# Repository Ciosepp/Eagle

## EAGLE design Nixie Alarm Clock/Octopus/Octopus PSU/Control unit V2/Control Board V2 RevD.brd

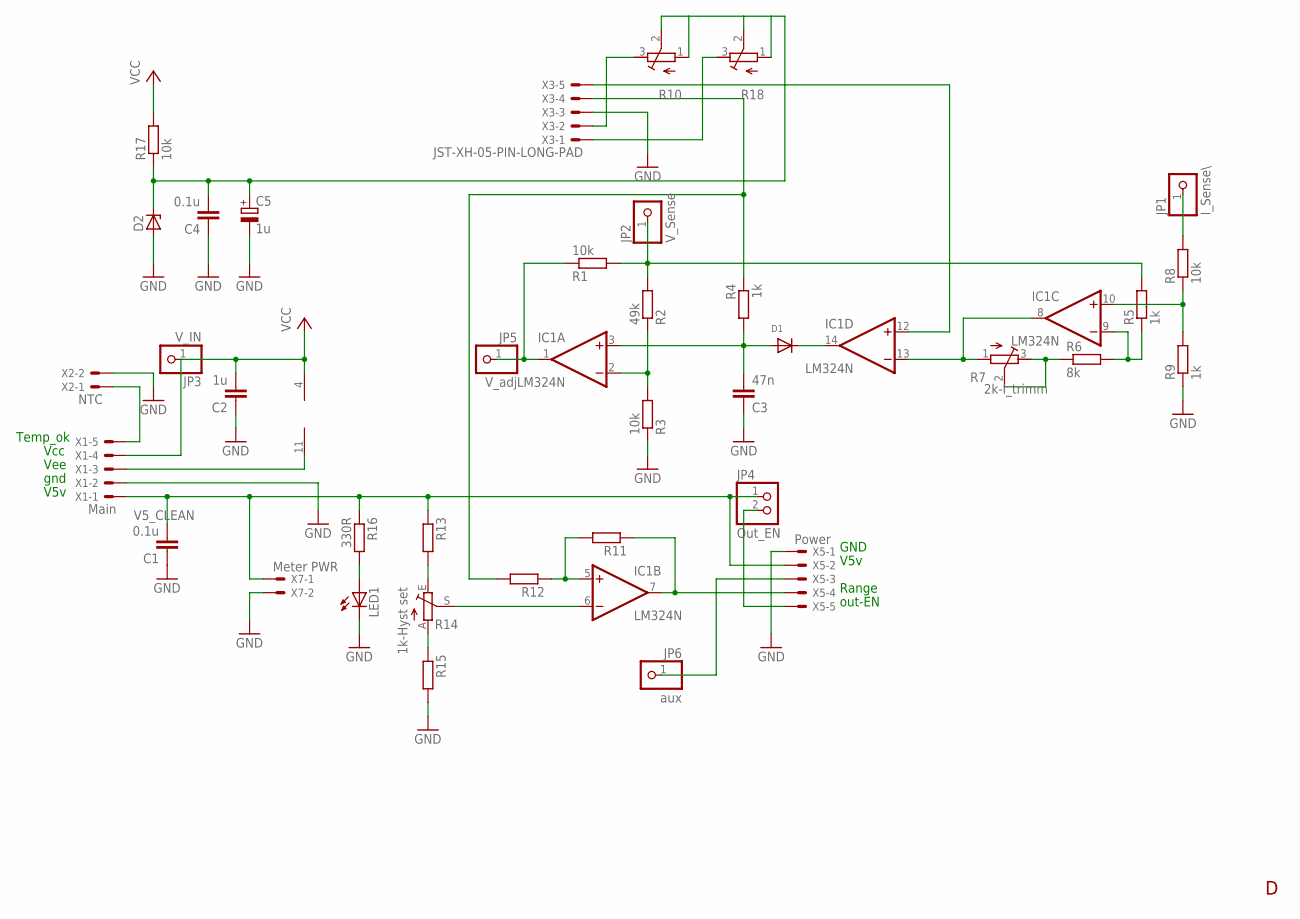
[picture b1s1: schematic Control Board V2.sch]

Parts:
C1, C4: 0.1u; C050-025X075
C2: 1u; C050-025X075
C3: 47n; C050-025X075
C5: 1u; E5-10,5
D1: DIODEDO-1N4148; DO-1N4148
D2: ZENER-DIODEDO35Z10; DO35Z10
IC1: LM324N; DIL14
JP1: I_Sense\; 1X01
JP2: V_Sense; 1X01
JP3: V_IN; 1X01
JP4: Out_EN; 1X02
JP5: V_adj; 1X01
JP6: aux; 1X01
LED1: LED3MM
R1, R3, R8, R17: 10k; 0204/7
R2: 49k; 0204/7
R4, R9: 1k; 0204/7
R5: 1k; 0204/5
R6: 8k; 0204V
R7: 2k-I_trimm; RTRIM64W
R10, R18: R-TRIMM64W; RTRIM64W
R11: R-EU_0204/5; 0204/5
R12, R13: R-EU_0204/2V; 0204V
R14: 1k-Hyst set; B25P
R15: R-EU_0204/7; 0204/7
R16: 330R; 0207/2V
X1: Main; JST-XH-05-PACKAGE-LONG-PAD
X2: NTC; JST-XH-02-PACKAGE-LONG-PAD
X3: JST-XH-05-PIN-LONG-PAD; JST-XH-05-PACKAGE-LONG-PAD
X5: Power; JST-XH-05-PACKAGE-LONG-PAD
X7: Meter PWR; JST-XH-02-PACKAGE-LONG-PAD

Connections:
GND: C1.1, C2.1, C3.1, C4.1, C5.-, D2.A, LED1.K (C), R3.1, R9.1, R15.2, X1.2, X2.2, X3.3, X5.1, X7.2
unnamed: D1.C, IC1.14 (OUT)
unnamed: X1.5, X2.1
unnamed: IC1.1 (OUT), JP5.1, R1.1
unnamed: JP6.1, X5.3
unnamed: IC1.2 (-IN), R2.1, R3.2
unnamed: C3.2, D1.A, IC1.3 (+IN), R4.2
unnamed: JP4.2, X5.5
unnamed: R6.1, R7.2 (S), R7.3 (E)
unnamed: IC1.9 (-IN), R5.1, R6.2
unnamed: IC1.8 (OUT), IC1.13 (-IN), R7.1 (A)
unnamed: JP1.1, R8.2
unnamed: LED1.A, R16.2
unnamed: IC1.11 (V-), X1.3
unnamed: IC1.12 (+IN), X3.5
unnamed: IC1.6 (-IN), R14.S
unnamed: R10.3 (E), X3.2
unnamed: R18.3 (E), X3.1
unnamed: JP2.1, R1.2, R2.2, R5.2
unnamed: IC1.7 (OUT), R11.1, X5.4
unnamed: IC1.5 (+IN), R11.2, R12.1
unnamed: R13.2, R14.E
unnamed: C4.2, C5.+, D2.C, R10.1 (A), R10.2 (S), R17.1, R18.1 (A), R18.2 (S)
unnamed: R14.A, R15.1
unnamed: R4.1, R12.2, X3.4
unnamed: IC1.10 (+IN), R8.1, R9.2
V5_CLEAN: C1.2, JP4.1, R13.1, R16.1, X1.1, X5.2, X7.1
VCC: C2.2, IC1.4 (V+), JP3.1, R17.2, X1.4

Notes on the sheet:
out-EN
GND
Range
Vcc
Vee
gnd
V5v
Temp_ok

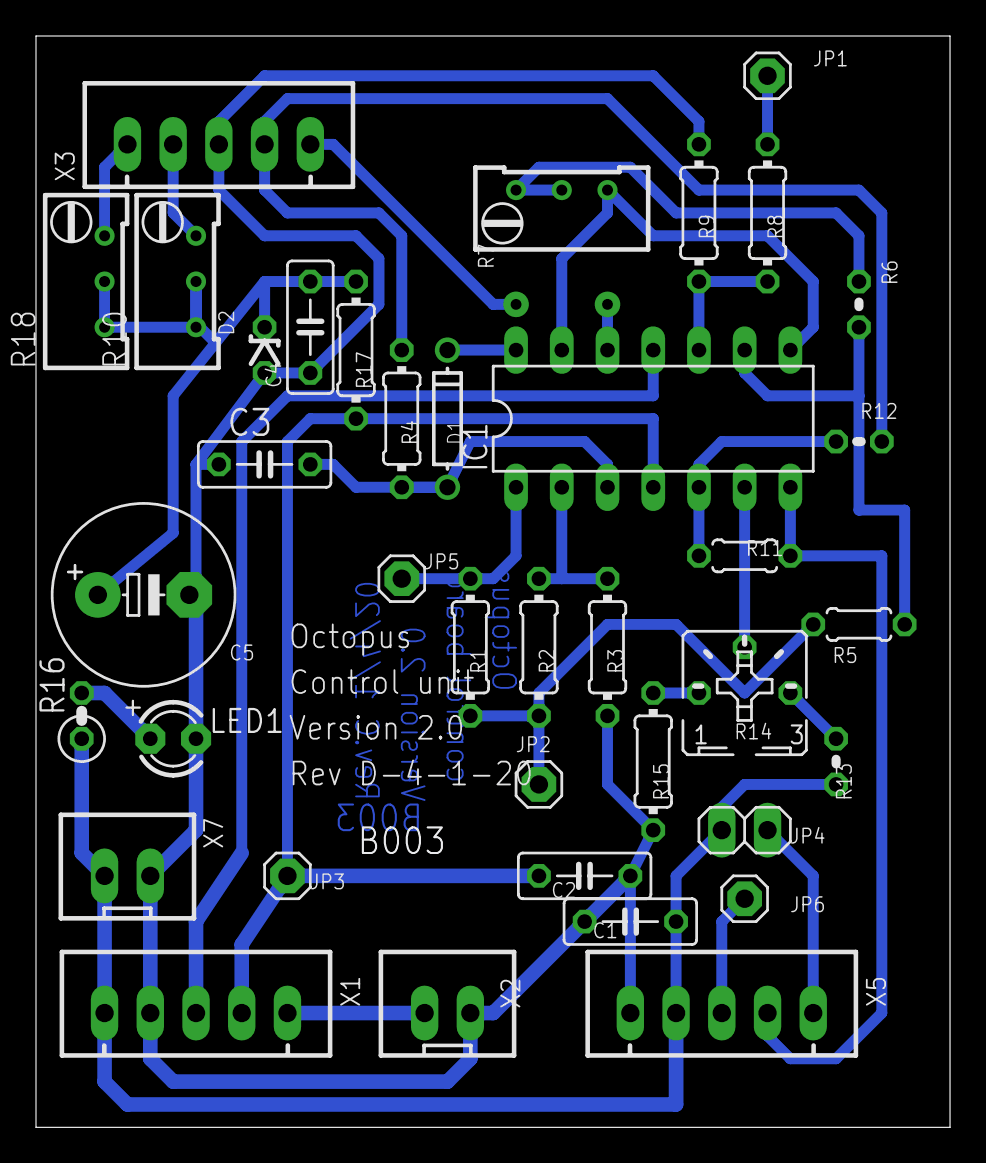
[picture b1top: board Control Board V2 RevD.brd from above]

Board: 2 copper layers, 50.8 x 60.6 mm, 38 parts (0 on the bottom side), 28 nets.

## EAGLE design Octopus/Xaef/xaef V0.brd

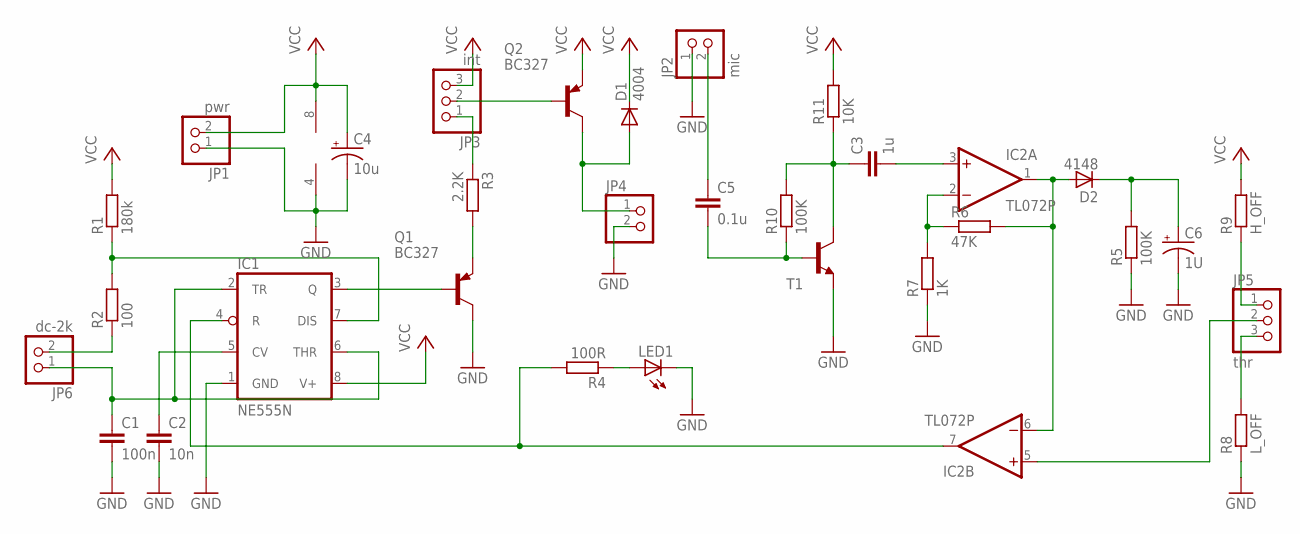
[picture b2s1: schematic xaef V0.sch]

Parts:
C1: 100n; C050-030X075
C2: 10n; C050-030X075
C3: 1u; C050-030X075
C4: 10u; E3,5-8
C5: 0.1u; C050-025X075
C6: 1U; E3,5-8
D1: 4004; D-2.5
D2: 4148; DIODE_DO35-7
IC1: NE555N; DIL08-ROUND
IC2: TL072P; DIL08
JP1: pwr; 1X02
JP2: mic; 1X02
JP3: int; 1X03
JP4: PINHD-1X2; 1X02
JP5: thr; 1X03
JP6: dc-2k; 1X02
LED1: LED5MM
Q1, Q2: BC327; TO92-EBC
R1: 180k; 0207/2V
R2: 100; 0207/2V
R3: 2.2K; 0207/2V
R4: 100R; 0207/2V
R5, R10: 100K; 0207/2V
R6: 47K; 0207/2V
R7: 1K; 0207/2V
R8: L_OFF; 0207/2V
R9: H_OFF; 0207/2V
R11: 10K; 0207/2V
T1: 2N3904-NPN-TO92-EBC; TO92-EBC

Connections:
GND: C1.2, C2.2, C4.-, C6.-, IC1.1 (GND), IC2.4 (V-), JP1.1, JP2.1, JP4.2, LED1.K (C), Q1.C, R5.1, R7.1, R8.1, T1.E
unnamed: IC1.7 (DIS), R1.1, R2.2
unnamed: IC1.3 (Q), Q1.B
unnamed: JP3.2, Q2.B
unnamed: Q1.E, R3.2
unnamed: D1.A, JP4.1, Q2.C
unnamed: C2.1, IC1.5 (CV)
unnamed: C1.1, IC1.2 (TR), IC1.6 (THR), JP6.1
unnamed: LED1.A, R4.1
unnamed: IC1.4 (R), IC2.7 (OUT), R4.2
unnamed: JP3.1, R3.1
unnamed: IC2.2 (-IN), R6.1, R7.2
unnamed: JP6.2, R2.1
unnamed: D2.A (C), IC2.1 (OUT), IC2.6 (-IN), R6.2
unnamed: C3.2, IC2.3 (+IN)
unnamed: C3.1, R10.2, R11.1, T1.C
unnamed: JP5.3, R8.2
unnamed: JP5.1, R9.1
unnamed: C5.2, R10.1, T1.B
unnamed: IC2.5 (+IN), JP5.2
unnamed: C6.+, D2.C (A), R5.2
unnamed: C5.1, JP2.2
VCC: C4.+, D1.C, IC1.8 (V+), IC2.8 (V+), JP1.2, JP3.3, Q2.E, R1.2, R9.2, R11.2

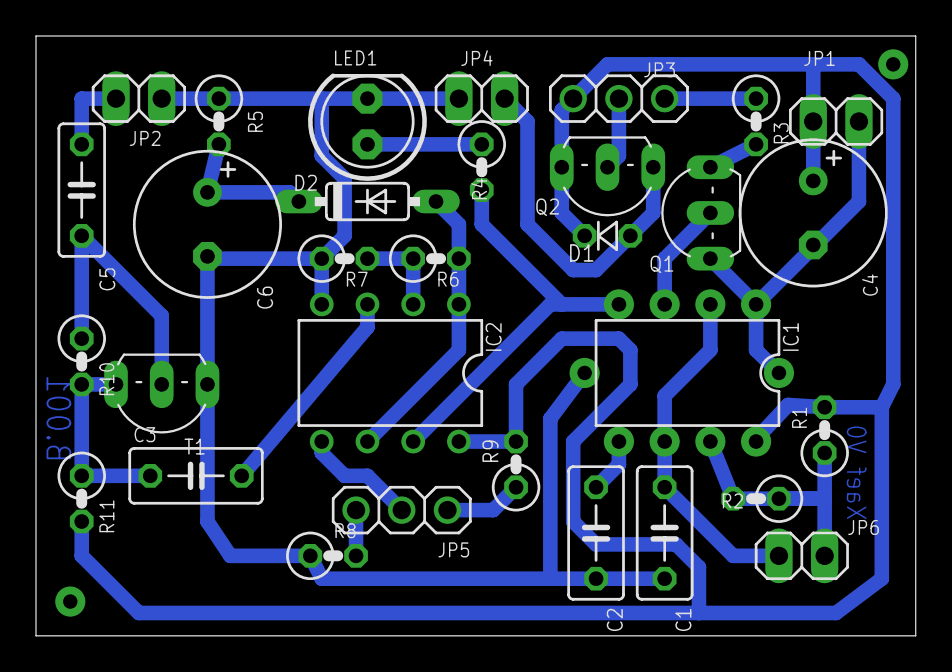
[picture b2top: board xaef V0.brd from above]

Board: 2 copper layers, 48.9 x 33.3 mm, 31 parts (0 on the bottom side), 23 nets.

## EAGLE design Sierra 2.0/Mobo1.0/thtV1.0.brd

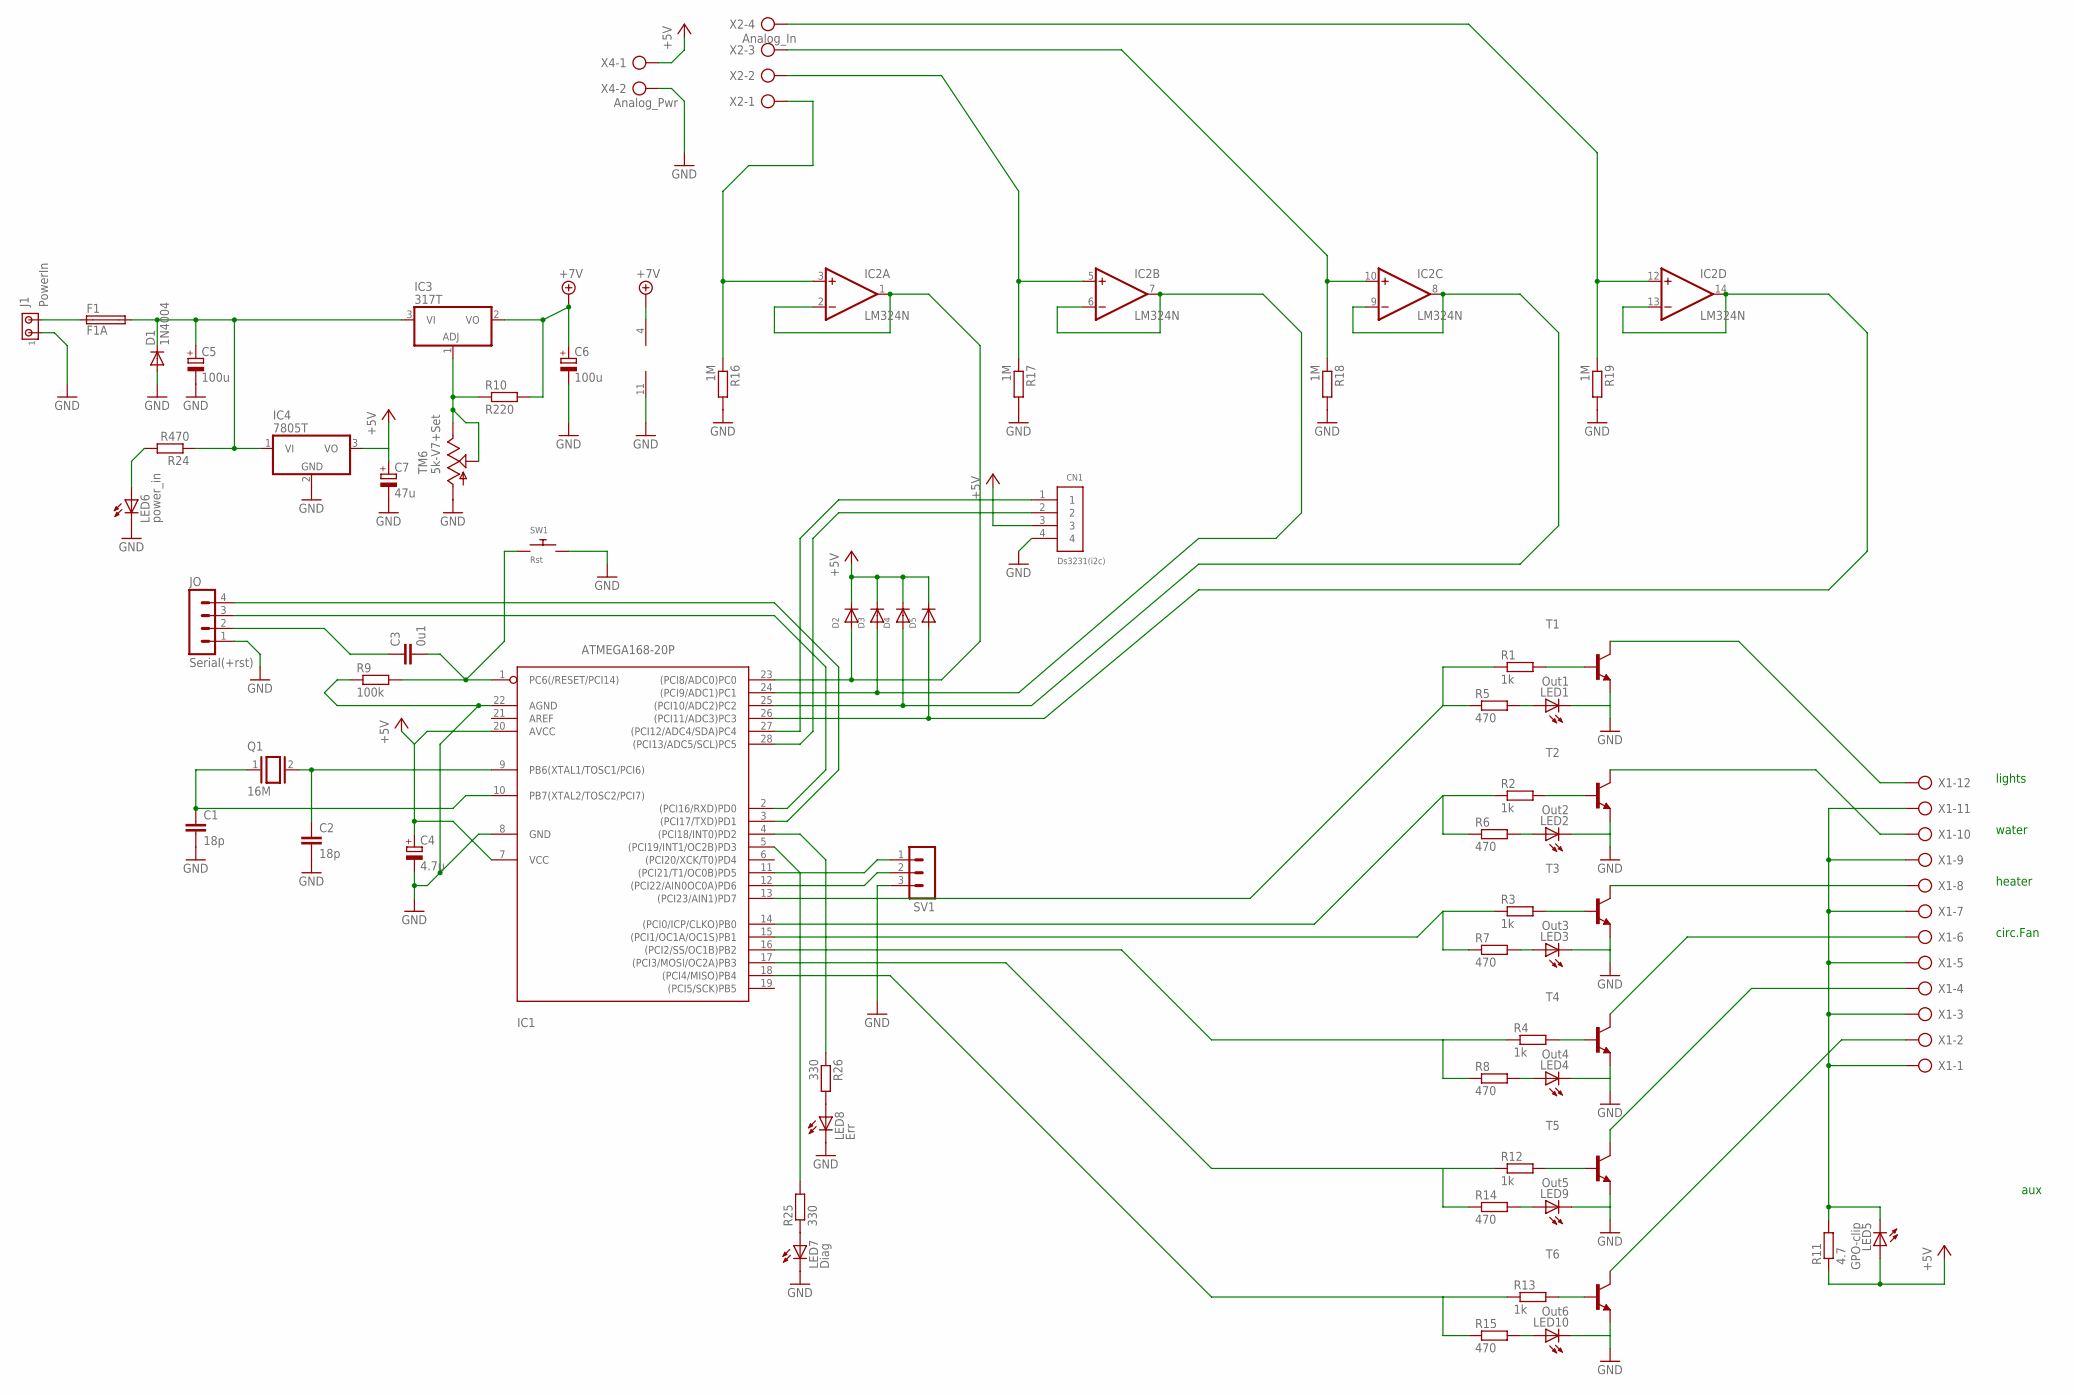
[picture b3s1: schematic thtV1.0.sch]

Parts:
C1, C2: 18p; C025-024X044
C3: 0u1; C050-030X075
C4: 4.7u; E5-10,5
C5: 100u; E5-10,5
C6: 100u; E3,5-8
C7: 47u; E2,5-6E
CN1: Ds3231(i2c); 1X04-BIG
D1: 1N4004; DO41-10
D2, D3, D4, D5: DIODEDO-1N4148; DO-1N4148
F1: F1A; GSH15
IC1: ATMEGA168-20P; DIL28-3
IC2: LM324N; DIL14
IC3: 317T; TO220H
IC4: 7805T; TO220H
J1: PowerIn; 1X2MTA
JO: Serial(+rst); MA04-1
LED1: Out1; LED3MM
LED2: Out2; LED3MM
LED3: Out3; LED3MM
LED4: Out4; LED3MM
LED5: GPO-clip; LED3MM
LED6: power_in; LED3MM
LED7: Diag; LED3MM
LED8: Err; LED3MM
LED9: Out5; LED3MM
LED10: Out6; LED3MM
Q1: 16M; QS
R1, R2, R3, R4, R12, R13: 1k; 0207/10
R5, R6, R7, R8, R14, R15: 470; 0204V
R9: 100k; 0207/10
R10: R220; 0207/10
R11: 4.7; 0207/10
R16, R17, R18, R19: 1M; 0204V
R24: R470; 0207/10
R25, R26: 330; 0207/2V
SV1: MA03-1
SW1: Rst; TACT_PANA-EVQ
T1, T2, T3, T4, T5, T6: BC547A-NPN-TO92-CBE; TO92-CBE
TM6: 5k-V7+Set; 6MM
X1: AK300/12
X2: Analog_In; AK300/4
X4: Analog_Pwr; AK300/2

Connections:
+5V: C4.+, C7.+, CN1.3, D2.C, D3.C, D4.C, D5.C, IC1.7 (VCC), IC1.20 (AVCC), IC4.3 (VO), LED5.A, R11.1, X4.1
+7V: C6.+, IC2.4 (V+), IC3.2 (VO), R10.2
GND: C1.2, C2.2, C4.-, C5.-, C6.-, C7.-, CN1.4, D1.A, IC1.8 (GND), IC1.22 (AGND), IC2.11 (V-), IC4.2 (GND), J1.1, JO.1, LED1.K (C), LED2.K (C), LED3.K (C), LED4.K (C), LED6.K (C), LED7.K (C), LED8.K (C), LED9.K (C), LED10.K (C), R9.1, R16.2, R17.2, R18.2, R19.2, SV1.3, SW1.P$2, T1.E, T2.E, T3.E, T4.E, T5.E, T6.E, TM6.A, X4.2
unnamed: C2.1, IC1.9 (PB6(XTAL1/TOSC1/PCI6)), Q1.2
unnamed: C1.1, IC1.10 (PB7(XTAL2/TOSC2/PCI7)), Q1.1
unnamed: R4.2, T4.B
unnamed: R3.2, T3.B
unnamed: LED8.A, R26.2
unnamed: LED3.A, R7.2
unnamed: LED2.A, R6.2
unnamed: LED1.A, R5.2
unnamed: LED4.A, R8.2
unnamed: R1.2, T1.B
unnamed: R2.2, T2.B
unnamed: IC1.16 ((PCI2/SS/OC1B)PB2), R4.1, R8.1
unnamed: IC2.10 (+IN), R18.1, X2.3
unnamed: IC1.15 ((PCI1/OC1A/OC1S)PB1), R3.1, R7.1
unnamed: IC1.14 ((PCI0/ICP/CLKO)PB0), R2.1, R6.1
unnamed: D3.A, IC1.24 ((PCI9/ADC1)PC1), IC2.6 (-IN), IC2.7 (OUT)
unnamed: IC1.5 ((PCI19/INT1/OC2B)PD3), R25.2
unnamed: IC1.4 ((PCI18/INT0)PD2), R26.1
unnamed: C3.1, JO.2
unnamed: IC3.1 (ADJ), R10.1, TM6.E, TM6.S
unnamed: IC1.2 ((PCI16/RXD)PD0), JO.3
unnamed: IC1.3 ((PCI17/TXD)PD1), JO.4
unnamed: F1.1, J1.2
unnamed: C5.+, D1.C, F1.2, IC3.3 (VI), IC4.1 (VI), R24.1
unnamed: C3.2, IC1.1 (PC6(/RESET/PCI14)), R9.2, SW1.P$1
unnamed: R13.2, T6.B
unnamed: R12.2, T5.B
unnamed: T1.C, X1.12
unnamed: T2.C, X1.10
unnamed: T3.C, X1.8
unnamed: T4.C, X1.6
unnamed: LED5.K (C), R11.2, X1.1, X1.3, X1.5, X1.7, X1.9, X1.11
unnamed: LED9.A, R14.2
unnamed: IC2.5 (+IN), R17.1, X2.2
unnamed: IC2.12 (+IN), R19.1, X2.4
unnamed: D2.A, IC1.23 ((PCI8/ADC0)PC0), IC2.1 (OUT), IC2.2 (-IN)
unnamed: LED10.A, R15.2
unnamed: D4.A, IC1.25 ((PCI10/ADC2)PC2), IC2.8 (OUT), IC2.9 (-IN)
unnamed: D5.A, IC1.26 ((PCI11/ADC3)PC3), IC2.13 (-IN), IC2.14 (OUT)
unnamed: IC1.18 ((PCI4/MISO)PB4), R13.1, R15.1
unnamed: IC1.17 ((PCI3/MOSI/OC2A)PB3), R12.1, R14.1
unnamed: IC2.3 (+IN), R16.1, X2.1
unnamed: T5.C, X1.4
unnamed: T6.C, X1.2
unnamed: LED6.A, R24.2
unnamed: LED7.A, R25.1
unnamed: CN1.1, IC1.27 ((PCI12/ADC4/SDA)PC4)
unnamed: CN1.2, IC1.28 ((PCI13/ADC5/SCL)PC5)
unnamed: IC1.11 ((PCI21/T1/OC0B)PD5), SV1.1
unnamed: IC1.13 ((PCI23/AIN1)PD7), R1.1, R5.1
unnamed: IC1.12 ((PCI22/AIN0OC0A)PD6), SV1.2

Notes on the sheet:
lights
water
heater
circ.Fan
aux

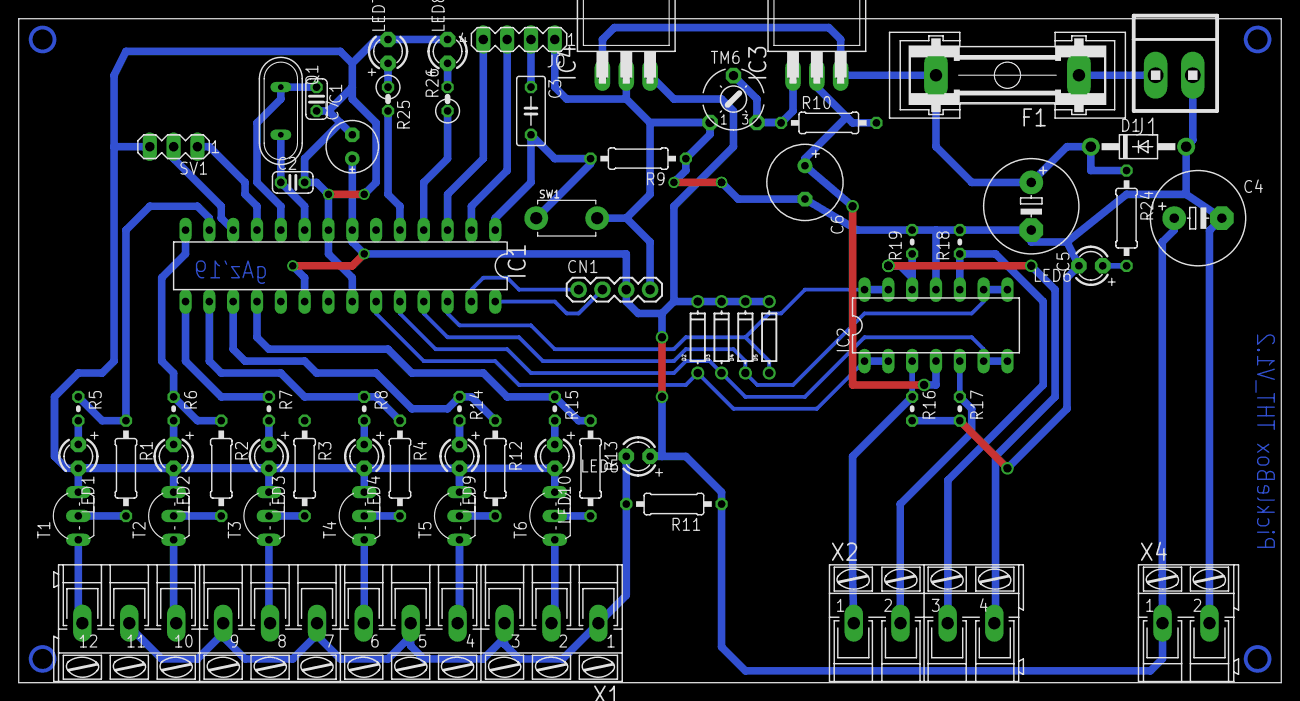
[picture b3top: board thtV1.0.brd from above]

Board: 2 copper layers, 134.6 x 70.8 mm, 65 parts (0 on the bottom side), 54 nets.

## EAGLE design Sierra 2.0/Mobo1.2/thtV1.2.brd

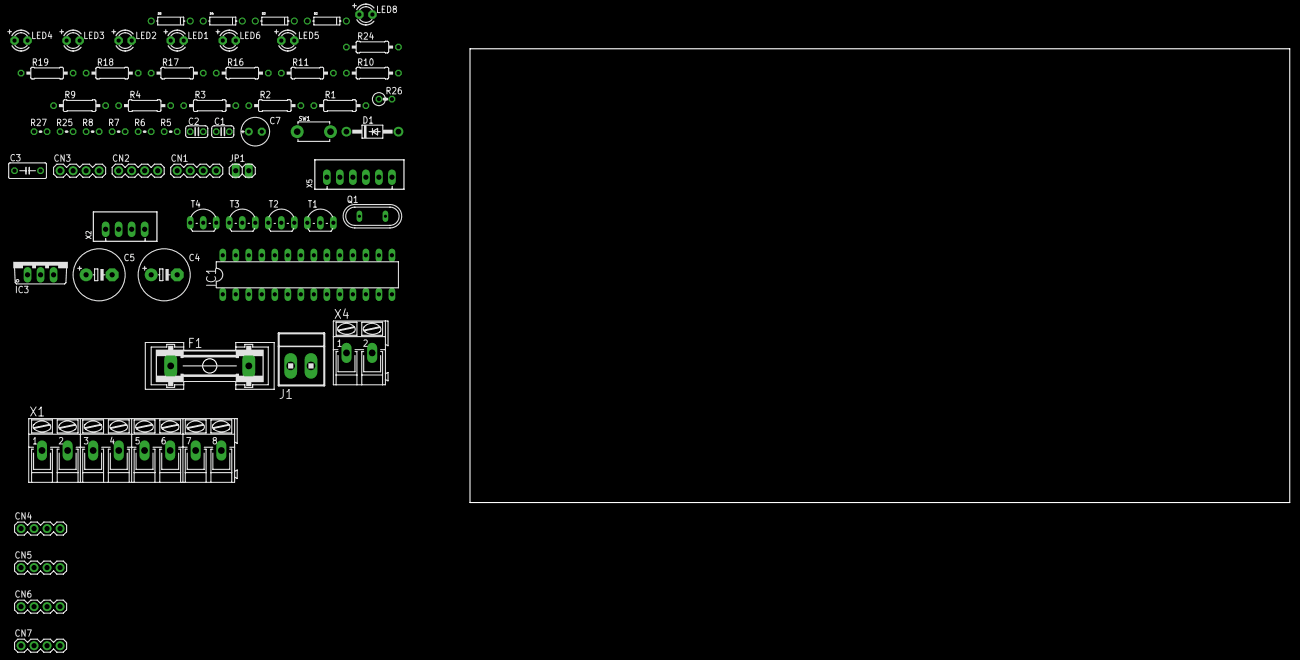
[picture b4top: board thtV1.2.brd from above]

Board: 2 copper layers, 160.0 x 88.6 mm, 59 parts (0 on the bottom side), 42 nets, no tracks yet.

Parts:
C1, C2: 18p; C025-024X044
C3: 0u1; C050-030X075
C4: 4.7u; E5-10,5
C5: 100u; E5-10,5
C7: 47u; E2,5-6E
CN1: Ds3231(i2c); 1X04-BIG
CN2: I2C-GPO; 1X04-BIG
CN3: I2C-APU; 1X04-BIG
CN4, CN5, CN6, CN7: 1X4-BIG; 1X04-BIG
D1: 1N4004; DO41-10
D2, D3, D4, D5: DO-1N4148
F1: F1A; GSH15
IC1: ATMEGA328; DIL28-3
IC3: 7805TV; TO220V
J1: PowerIn; 1X2MTA
JP1: Main Pushbutton; 1X02
LED1: Out1; LED3MM
LED2: Out2; LED3MM
LED3: Out3; LED3MM
LED4: Out4; LED3MM
LED5: GPO-clip; LED3MM
LED6: pwr_ok; LED3MM
LED8: Err; LED3MM
Q1: 16M; QS
R1, R2, R3, R4: 1k; 0207/10
R5, R6, R7, R8: 470; 0204V
R9: 100k; 0207/10
R10: 0R1; 0207/10
R11: 4R7; 0207/10
R16, R17, R18, R19: 1M; 0207/10
R24: 470; 0207/10
R25, R27: 10k; 0204V
R26: 330; 0207/2V
SW1: Rst; TACT_PANA-EVQ
T1, T2, T3, T4: 2N2222; TO92-EBC-OVAL
X1: GPO; AK300/8
X2: Serial_port; JST-XH-04-PACKAGE-LONG-PAD
X4: Analog_Pwr; AK300/2
X5: Sd_module; JST-XH-06-PACKAGE-LONG-PAD

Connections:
+5V: C4.+, C7.+, CN1.3, CN2.3, CN3.3, CN4.3, CN5.3, CN6.3, CN7.3, D2.C, D3.C, D4.C, D5.C, IC1.7, IC1.20, IC3.3, LED5.A, R10.2, R11.1, R25.1, R27.1, X5.2
GND: C1.2, C2.2, C4.-, C5.-, C7.-, CN1.4, CN2.4, CN3.4, CN4.4, CN5.4, CN6.4, CN7.4, D1.A, IC1.8, IC1.22, IC3.2, J1.1, JP1.2, LED1.K, LED2.K, LED3.K, LED4.K, LED6.K, LED8.K, R9.1, R16.2, R17.2, R18.2, R19.2, SW1.P$2, T1.E, T2.E, T3.E, T4.E, X2.1, X4.2, X5.1
I2C_SCL: CN1.2, CN2.2, CN3.2, IC1.28, R27.2
I2C_SDA: CN1.1, CN2.1, CN3.1, IC1.27, R25.2
unnamed: C2.1, IC1.9, Q1.2
unnamed: R4.2, T4.B
unnamed: R3.2, T3.B
unnamed: LED8.A, R26.2
unnamed: LED3.A, R7.2
unnamed: LED2.A, R6.2
unnamed: LED1.A, R5.2
unnamed: LED4.A, R8.2
unnamed: R1.2, T1.B
unnamed: R2.2, T2.B
unnamed: IC1.12, R4.1, R8.1
unnamed: R10.1, X4.1
unnamed: IC1.13, R3.1, R7.1
unnamed: IC1.14, R2.1, R6.1
unnamed: CN5.1, D3.A, IC1.24, R17.1
unnamed: IC1.11, JP1.1
unnamed: T3.C, X1.4
unnamed: C1.1, IC1.10, Q1.1
unnamed: IC1.6, R26.1
unnamed: C3.1, X2.2
unnamed: IC1.18, X5.3
unnamed: IC1.19, X5.5
unnamed: IC1.2, X2.3
unnamed: IC1.3, X2.4
unnamed: IC1.17, X5.4
unnamed: F1.1, J1.2
unnamed: C5.+, D1.C, F1.2, IC3.1, R24.1
unnamed: C3.2, IC1.1, R9.2, SW1.P$1
unnamed: IC1.16, X5.6
unnamed: T1.C, X1.8
unnamed: T2.C, X1.6
unnamed: T4.C, X1.2
unnamed: LED5.K, R11.2, X1.1, X1.3, X1.5, X1.7
unnamed: CN7.1, D5.A, IC1.26, R19.1
unnamed: CN4.1, D2.A, IC1.23, R16.1
unnamed: CN6.1, D4.A, IC1.25, R18.1
unnamed: LED6.A, R24.2
unnamed: IC1.15, R1.1, R5.1

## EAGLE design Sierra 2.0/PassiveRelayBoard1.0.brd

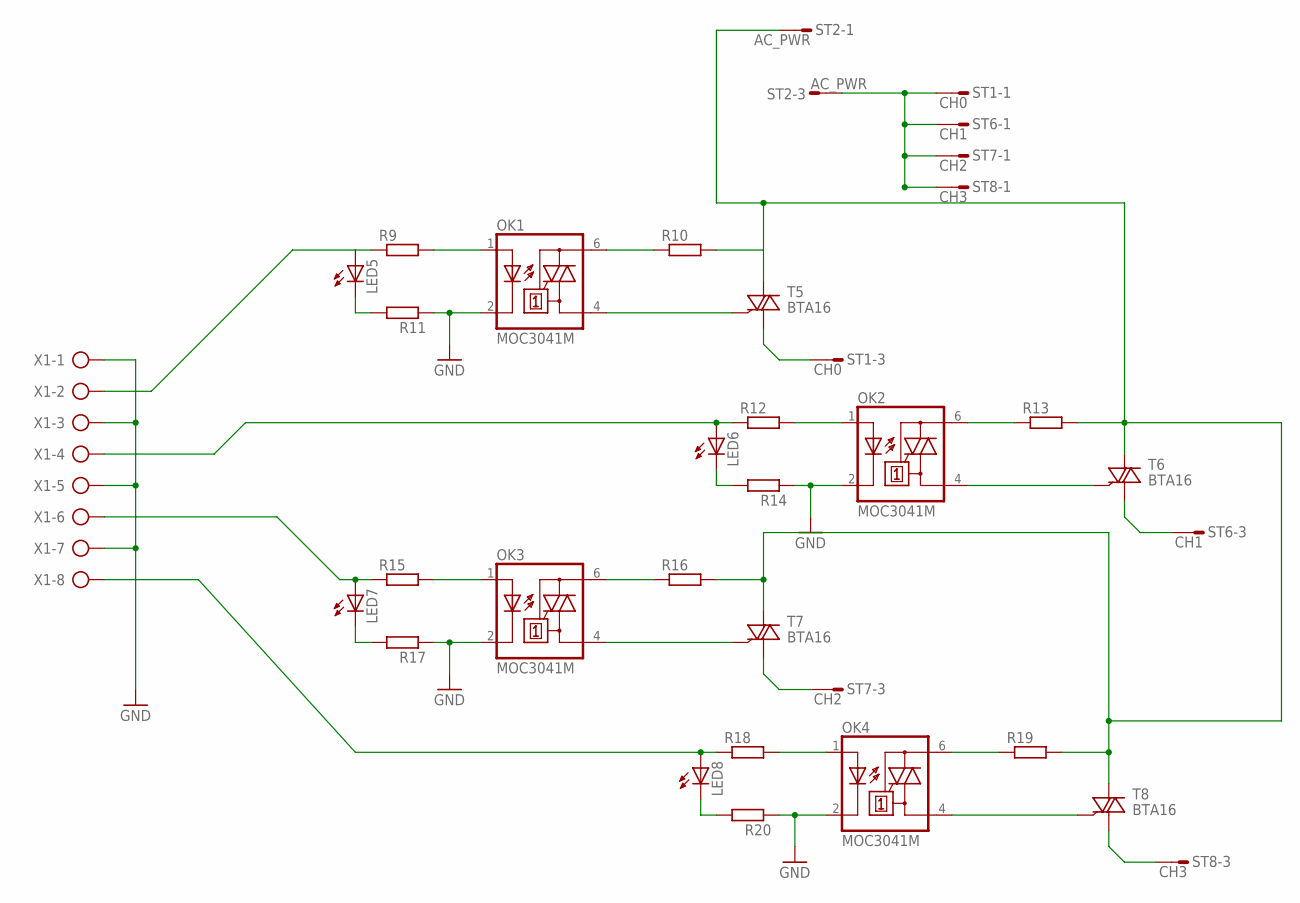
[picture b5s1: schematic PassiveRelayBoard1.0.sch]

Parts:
LED5, LED6, LED7, LED8: LED3MM
OK1, OK2, OK3, OK4: MOC3041M; DIL06
R9, R12, R15, R18: R-EU_0207/2V; 0207/2V
R10, R13, R16, R19: R-EU_0207/7; 0207/7
R11, R14, R17, R20: R-EU_0204/2V; 0204V
ST1: CH0; MSF3
ST2: AC_PWR; MSF3
ST6: CH1; MSF3
ST7: CH2; MSF3
ST8: CH3; MSF3
T5, T6, T7, T8: BTA16; TO220BV
X1: AK300/8

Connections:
GND: OK1.2 (C), OK2.2 (C), OK3.2 (C), OK4.2 (C), R11.1, R14.1, R17.1, R20.1, X1.1, X1.3, X1.5, X1.7
unnamed: R10.2, R13.2, R16.2, R19.2, ST2.1, T5.T2 (A2), T6.T2 (A2), T7.T2 (A2), T8.T2 (A2)
unnamed: ST1.1, ST2.3, ST6.1, ST7.1, ST8.1
unnamed: LED5.A, R9.1, X1.2
unnamed: OK1.1 (A), R9.2
unnamed: ST1.3, T5.T1 (A1)
unnamed: OK1.4 (A1), T5.G
unnamed: OK1.6 (A2), R10.1
unnamed: LED5.K (C), R11.2
unnamed: LED6.A, R12.1, X1.4
unnamed: OK2.1 (A), R12.2
unnamed: OK2.4 (A1), T6.G
unnamed: OK2.6 (A2), R13.1
unnamed: ST6.3, T6.T1 (A1)
unnamed: LED6.K (C), R14.2
unnamed: LED7.A, R15.1, X1.6
unnamed: OK3.1 (A), R15.2
unnamed: OK3.4 (A1), T7.G
unnamed: OK3.6 (A2), R16.1
unnamed: ST7.3, T7.T1 (A1)
unnamed: LED7.K (C), R17.2
unnamed: LED8.A, R18.1, X1.8
unnamed: OK4.1 (A), R18.2
unnamed: OK4.4 (A1), T8.G
unnamed: OK4.6 (A2), R19.1
unnamed: ST8.3, T8.T1 (A1)
unnamed: LED8.K (C), R20.2

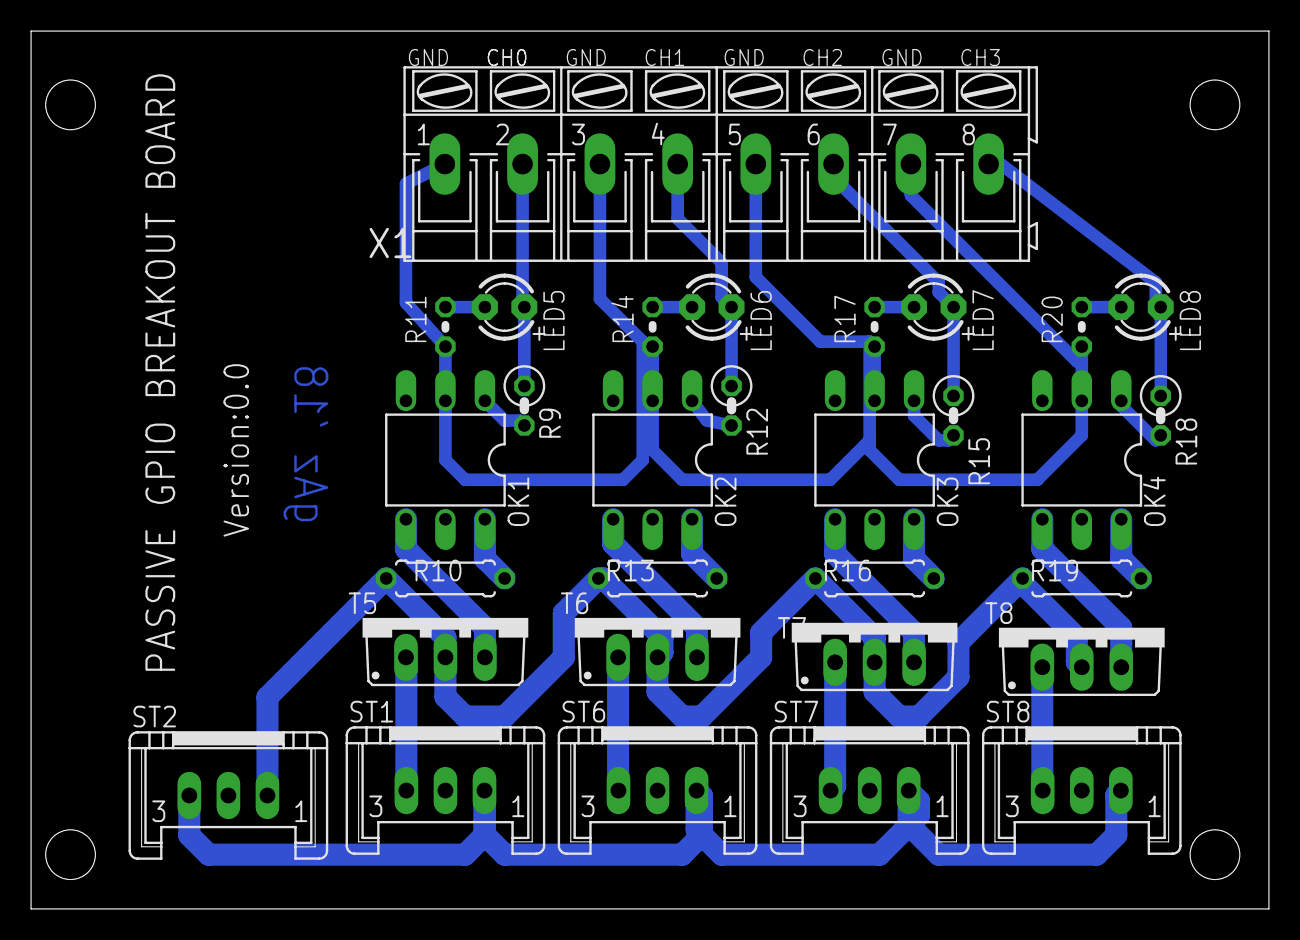
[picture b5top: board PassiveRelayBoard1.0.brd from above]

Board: 2 copper layers, 79.7 x 56.5 mm, 30 parts (0 on the bottom side), 27 nets.
